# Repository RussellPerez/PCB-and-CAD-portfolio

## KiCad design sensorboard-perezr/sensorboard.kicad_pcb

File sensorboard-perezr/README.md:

# sensorboard-perezr
IMU sensor board

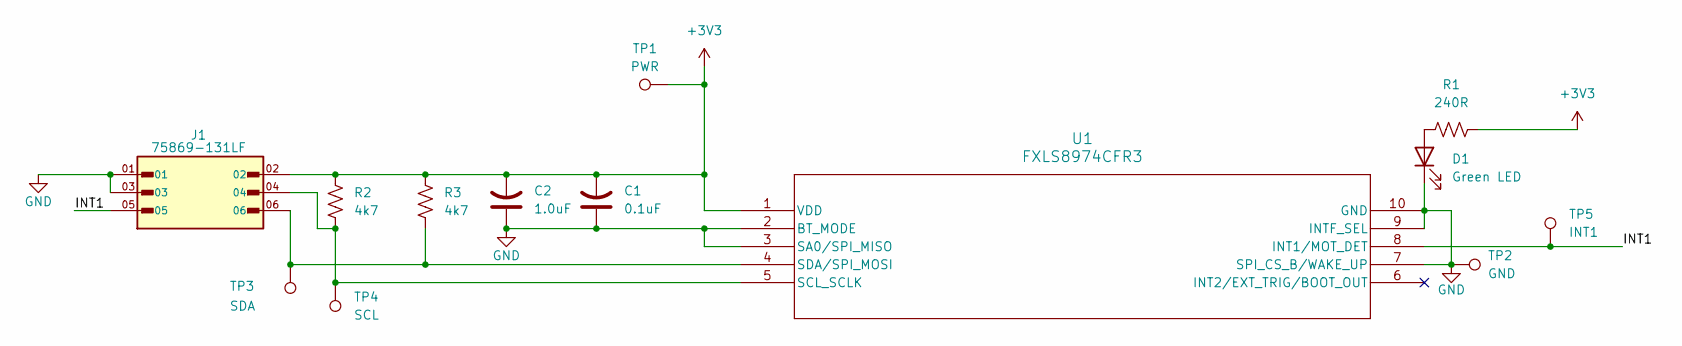
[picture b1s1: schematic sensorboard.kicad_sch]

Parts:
C1: 0.1uF; C_0805_2012Metric_Pad1.18x1.45mm_HandSolder
C2: 1.0uF; C_0805_2012Metric_Pad1.18x1.45mm_HandSolder
D1: Green LED; LED_0805_2012Metric_Pad1.15x1.40mm_HandSolder
J1: 75869-131LF; AMPHENOL_75869-131LF; PARTREV BT
R1: 240R; R_0805_2012Metric_Pad1.20x1.40mm_HandSolder
R2, R3: 4k7; R_0805_2012Metric_Pad1.20x1.40mm_HandSolder
TP1: PWR; TestPoint_THTPad_2.0x2.0mm_Drill1.0mm
TP2: GND; TestPoint_THTPad_2.0x2.0mm_Drill1.0mm
TP3: SDA; TestPoint_THTPad_2.0x2.0mm_Drill1.0mm
TP4: SCL; TestPoint_THTPad_2.0x2.0mm_Drill1.0mm
TP5: INT1; TestPoint_THTPad_2.0x2.0mm_Drill1.0mm
U1: FXLS8974CFR3; FXLS8974CFR3_NXP-M

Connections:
+3V3: C1.2, C2.2, J1.02, R1.2, R2.1, R3.1, TP1.1, U1.1 (VDD)
/INT1: J1.05, TP5.1, U1.8 (INT1/MOT_DET)
GND: C1.1, C2.1, D1.1 (K), J1.01, J1.03, TP2.1, U1.2 (BT_MODE), U1.3 (SA0/SPI_MISO), U1.7 (SPI_CS_B/WAKE_UP), U1.9 (INTF_SEL), U1.10 (GND)
unnamed: D1.2 (A), R1.1
unnamed: J1.04, R2.2, TP4.1, U1.5 (SCL_SCLK)
unnamed: J1.06, R3.2, TP3.1, U1.4 (SDA/SPI_MOSI)

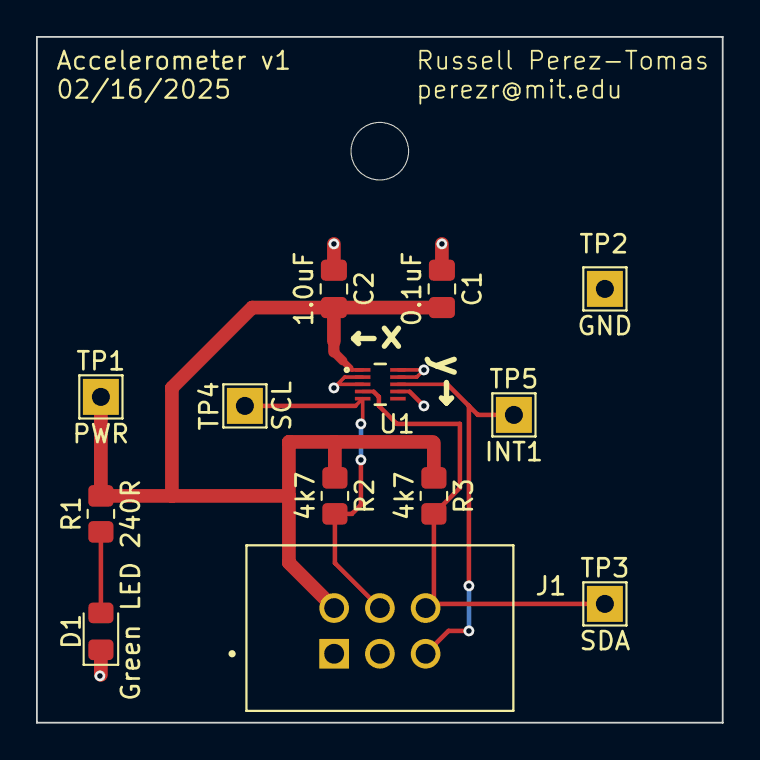
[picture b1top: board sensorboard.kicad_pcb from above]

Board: 2 copper layers, 38.1 x 38.1 mm, 13 parts (0 on the bottom side), 6 nets.

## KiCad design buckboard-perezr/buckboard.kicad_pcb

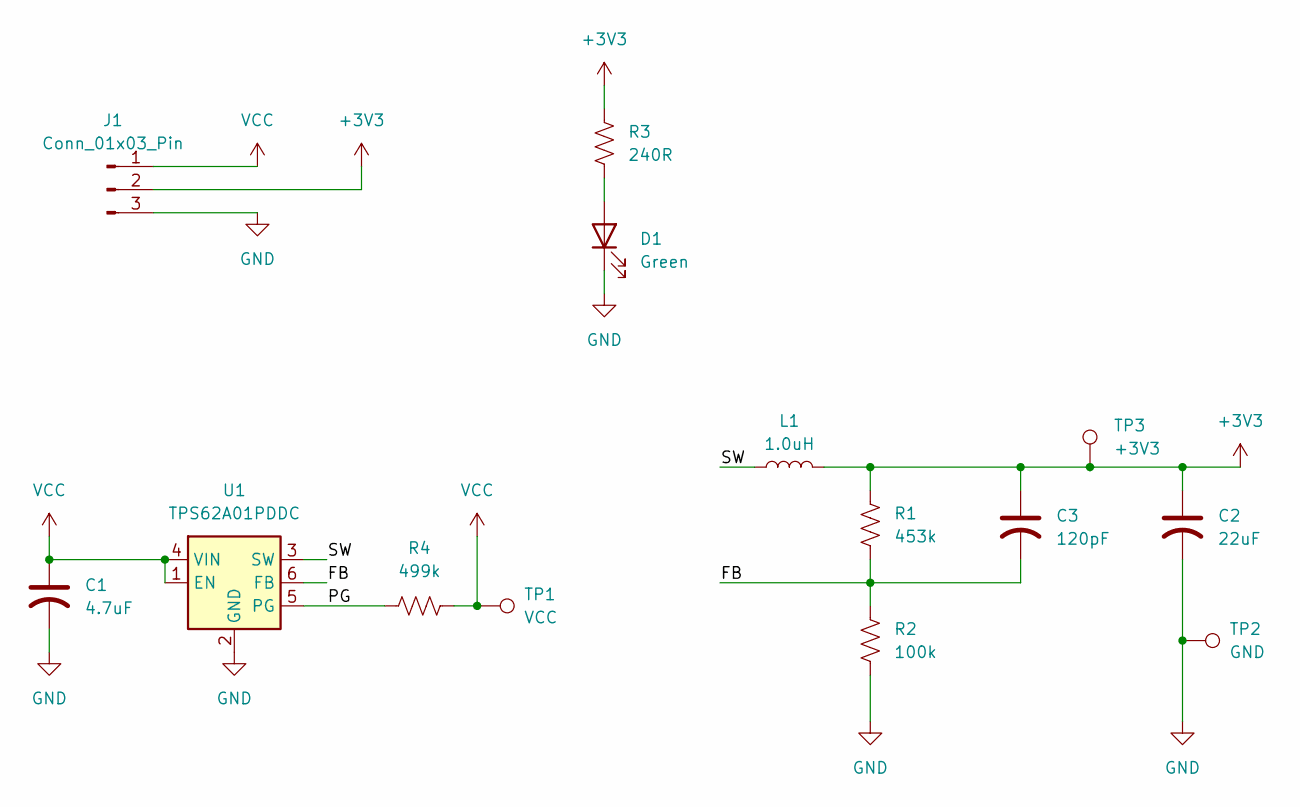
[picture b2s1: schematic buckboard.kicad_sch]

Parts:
C1: 4.7uF; C_0805_2012Metric_Pad1.18x1.45mm_HandSolder
C2: 22uF; C_0805_2012Metric_Pad1.18x1.45mm_HandSolder
C3: 120pF; C_0805_2012Metric_Pad1.18x1.45mm_HandSolder
D1: Green; LED_0805_2012Metric_Pad1.15x1.40mm_HandSolder
J1: Conn_01x03_Pin; PinSocket_1x03_P2.54mm_Horizontal
L1: 1.0uH; L_1008_2520Metric_Pad1.43x2.20mm_HandSolder
R1: 453k; R_0805_2012Metric_Pad1.20x1.40mm_HandSolder
R2: 100k; R_0805_2012Metric_Pad1.20x1.40mm_HandSolder
R3: 240R; R_0805_2012Metric_Pad1.20x1.40mm_HandSolder
R4: 499k; R_0805_2012Metric_Pad1.20x1.40mm_HandSolder
TP1: VCC; TestPoint_THTPad_2.0x2.0mm_Drill1.0mm
TP2: GND; TestPoint_THTPad_2.0x2.0mm_Drill1.0mm
TP3: +3V3; TestPoint_THTPad_2.0x2.0mm_Drill1.0mm
U1: TPS62A01PDDC; SOT-23-6

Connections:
+3V3: C2.1, C3.1, J1.2, L1.2, R1.1, R3.2, TP3.1
/FB: C3.2, R1.2, R2.1, U1.6 (FB)
/PG: R4.1, U1.5 (PG)
/SW: L1.1, U1.3 (SW)
GND: C1.2, C2.2, D1.1 (K), J1.3, R2.2, TP2.1, U1.2 (GND)
unnamed: D1.2 (A), R3.1
VCC: C1.1, J1.1, R4.2, TP1.1, U1.1 (EN), U1.4 (VIN)

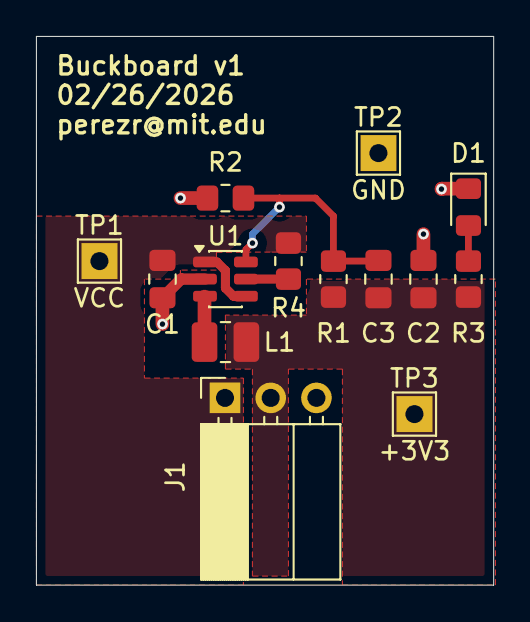
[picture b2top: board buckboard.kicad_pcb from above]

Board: 2 copper layers, 25.4 x 30.5 mm, 14 parts (0 on the bottom side), 7 nets.
